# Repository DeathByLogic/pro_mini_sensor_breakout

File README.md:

# pro_mini_sensor_breakout
Arduino Pro Mini sensor breakout board.

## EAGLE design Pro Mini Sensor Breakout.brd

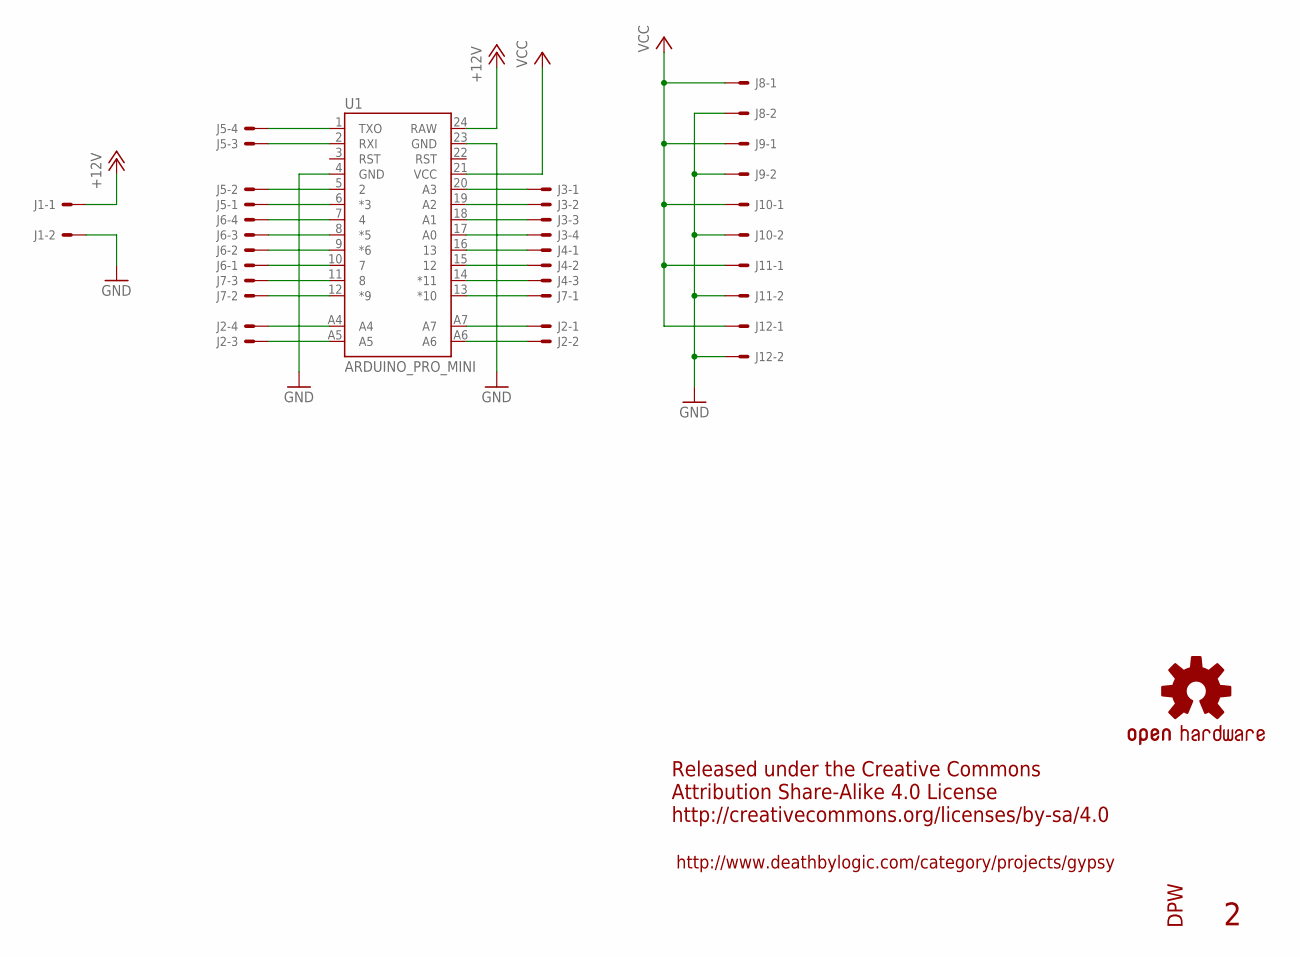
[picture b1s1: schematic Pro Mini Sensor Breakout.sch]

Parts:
J1, J8, J9, J10, J11, J12: 22-27-2021-02; 6410-02
J2, J3, J5, J6: 22-27-2041-04; 6410-04
J4, J7: 22-27-2031-03; 6410-03
LOGO2: OSHW-LOGOM; OSHW-LOGO-M
U1: ARDUINO_PRO_MINI
U$6: PENGUIN_LOGOSILKSCREEN; PENGUIN_SILKSCREEN

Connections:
+12V: J1.1, U1.24 (RAW)
GND: J1.2, J8.2, J9.2, J10.2, J11.2, J12.2, U1.4 (GND), U1.23 (GND)
unnamed: J2.4, U1.A4
unnamed: J2.3, U1.A5
unnamed: J2.1, U1.A7
unnamed: J2.2, U1.A6
unnamed: J3.1, U1.20 (A3)
unnamed: J3.2, U1.19 (A2)
unnamed: J3.3, U1.18 (A1)
unnamed: J3.4, U1.17 (A0)
unnamed: J4.1, U1.16 (13)
unnamed: J4.2, U1.15 (12)
unnamed: J4.3, U1.14 (*11)
unnamed: J5.4, U1.1 (TXO)
unnamed: J5.3, U1.2 (RXI)
unnamed: J5.2, U1.5 (2)
unnamed: J5.1, U1.6 (*3)
unnamed: J6.4, U1.7 (4)
unnamed: J6.3, U1.8 (*5)
unnamed: J6.2, U1.9 (*6)
unnamed: J6.1, U1.10 (7)
unnamed: J7.3, U1.11 (8)
unnamed: J7.2, U1.12 (*9)
unnamed: J7.1, U1.13 (*10)
VCC: J8.1, J9.1, J10.1, J11.1, J12.1, U1.21 (VCC)

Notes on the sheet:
http://www.deathbylogic.com/category/projects/gypsy
Released under the Creative Commons Attribution Share-Alike 4.0 License http://creativecommons.org/licenses/by-sa/4.0

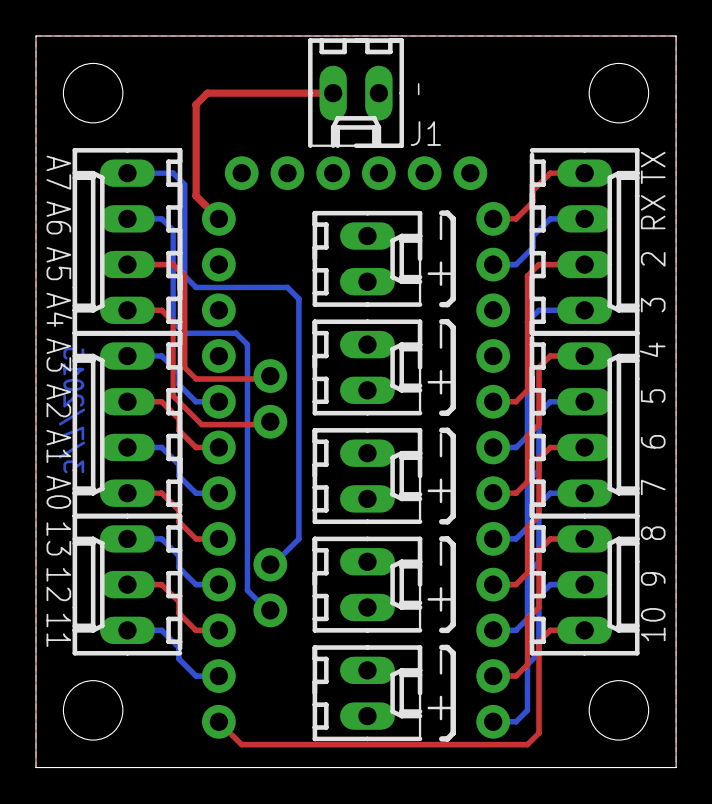
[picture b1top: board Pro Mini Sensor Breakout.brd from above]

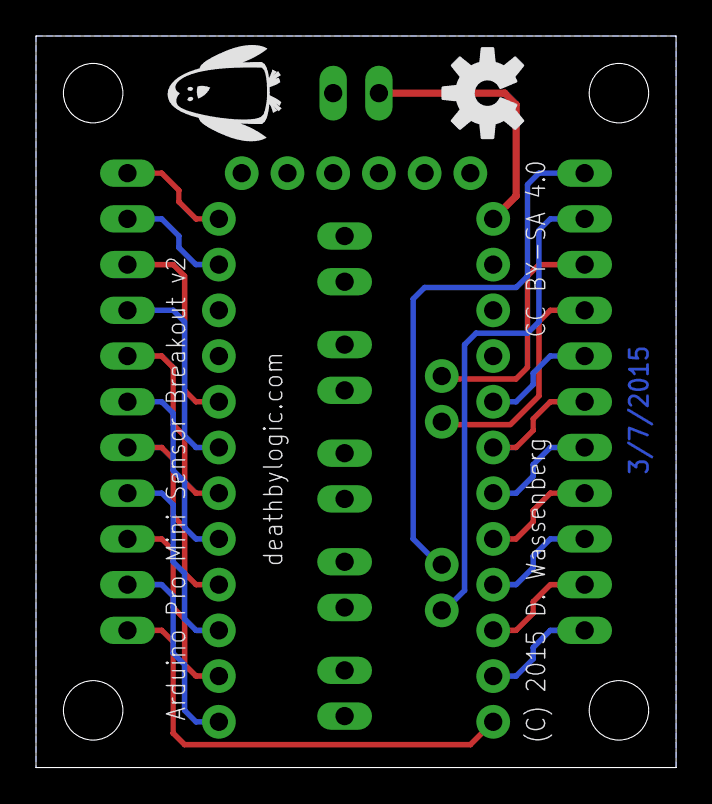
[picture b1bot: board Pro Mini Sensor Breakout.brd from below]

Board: 2 copper layers, 35.6 x 40.6 mm, 19 parts (3 on the bottom side), 25 nets.

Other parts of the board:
U$2, U$3, U$4, U$5: STAND-OFF

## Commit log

2015-02-20 Initial add of Pro Mini Sensor Breakout v1.
2015-03-15 Corrected mis-wire of A4 & A5.
2015-05-25 Added Eagle project file

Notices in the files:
Pro Mini Sensor Breakout.brd:
(C) 2015 D. Wassenberg
CC BY-SA 4.0
parts and their libraries:
SparkFun-Boards: Licensing: CC v3.0 Share-Alike You are welcome to use this library for commercial purposes.
